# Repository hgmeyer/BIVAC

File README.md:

# BIVAC
While navigating their environments it is essential for autonomous mobile systems to actively avoid collisions with obstacles. Flying insects perform this behavioural task with ease relying mainly on information the visual system provides. BIVAC (Bio-Inspired Visual Avoidance of Collisions) is a low-cost collision avoidance system based on the extraction of nearness information from visual motion. The system allows an autonomous mobile agent to navigate in cluttered environments while actively avoiding obstacles.

**Please note:** This is the repository for a project that will be hosted on [hackaday.io](http://hackaday.io/). Please visit the [project page](https://hackaday.io/project/13301-bivac-bio-inspired-visual-collision-avoidance/) for more information.

<br />This work is licensed under a <a rel="license" href="http://creativecommons.org/licenses/by-sa/4.0/">Creative Commons Attribution-ShareAlike 4.0 International License</a>.

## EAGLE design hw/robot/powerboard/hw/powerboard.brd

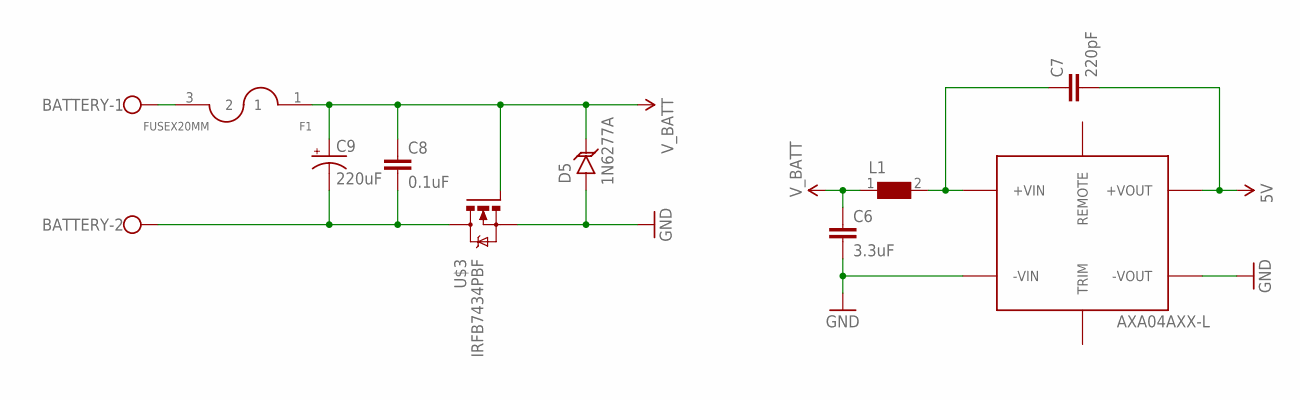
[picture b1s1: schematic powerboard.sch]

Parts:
BATTERY: W237-102
C6: 3.3uF; 1210
C7: 220pF; C1808
C8: 0.1uF; 0603-CAP
C9: 220uF; PANASONIC_G
D5: 1N6277A
F1: FUSEX20MM; FUSE_5MM
L1: WE-HCI-744314650_7030/7040/7050; WE-HCI_7030/7040/7050
U$2: AXA04AXX-L
U$3: IRFB7434PBF

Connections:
5V: C7.2, U$2.+VOUT
GND: C6.2, D5.A, U$2.-VIN, U$2.-VOUT, U$3.SOURCE (S)
unnamed: C7.1, L1.2, U$2.+VIN
unnamed: BATTERY.1, F1.3 (2)
unnamed: BATTERY.2, C8.2, C9.-, U$3.DRAIN (D)
V_BATT: C6.1, C8.1, C9.+, D5.C, F1.1, L1.1, U$3.GATE (G)

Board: 2 copper layers, 10 parts (0 on the bottom side), 6 nets, no tracks yet.

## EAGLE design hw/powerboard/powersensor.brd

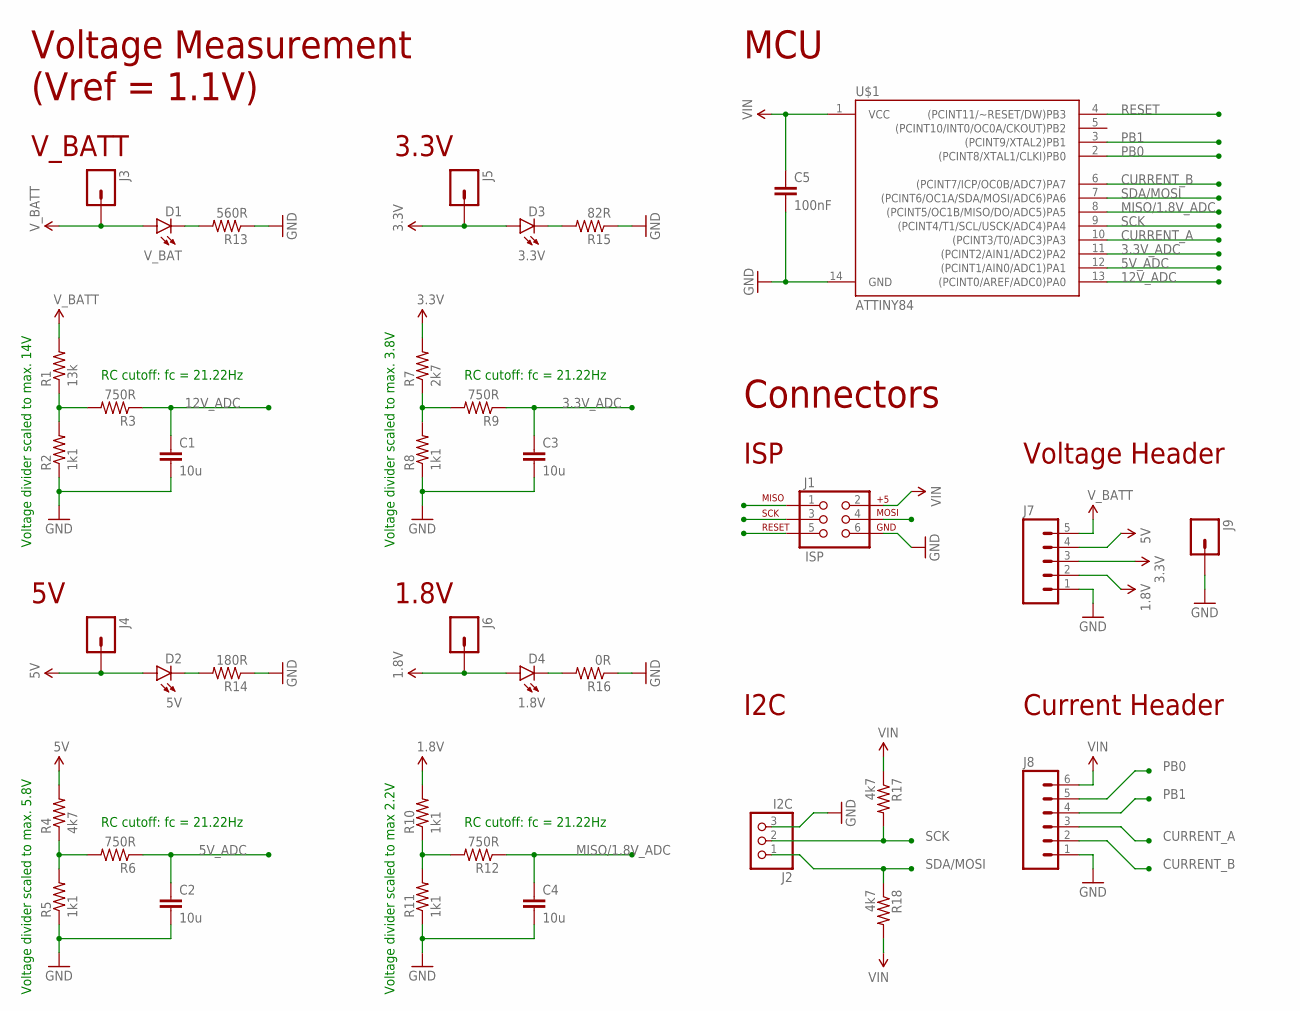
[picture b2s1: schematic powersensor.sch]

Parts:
C1, C2, C3, C4: 10u; 0603-CAP
C5: 100nF; 0603-CAP
D1: V_BAT; LED-0603
D2: 5V; LED-0603
D3: 3.3V; LED-0603
D4: 1.8V; LED-0603
J1: ISP; 2X3
J2: I2C; 1X03/90
J3, J4, J5, J6, J9: M01PTH; 1X01
J7: M05PTH; 1X05
J8: M06SILK_FEMALE_PTH; 1X06
R1: 13k; 0603-RES
R2, R5, R8, R10, R11: 1k1; 0603-RES
R3, R6, R9, R12: 750R; 0603-RES
R4, R17, R18: 4k7; 0603-RES
R7: 2k7; 0603-RES
R13: 560R; 0603-RES
R14: 180R; 0603-RES
R15: 82R; 0603-RES
R16: 0R; 0603-RES
U$1: ATTINY84; SO14

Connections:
1.8V: D4.A, J6.1, J7.2, R10.2
3.3V: D3.A, J5.1, J7.3, R7.2
3.3V_ADC: C3.1, R9.1, U$1.11 ((PCINT2/AIN1/ADC2)PA2)
5V: D2.A, J4.1, J7.4, R4.2
5V_ADC: C2.1, R6.1, U$1.12 ((PCINT1/AIN0/ADC1)PA1)
12V_ADC: C1.1, R3.1, U$1.13 ((PCINT0/AREF/ADC0)PA0)
CURRENT_A: J8.3, U$1.10 ((PCINT3/T0/ADC3)PA3)
CURRENT_B: J8.2, U$1.6 ((PCINT7/ICP/OC0B/ADC7)PA7)
GND: C1.2, C2.2, C3.2, C4.2, C5.2, J1.6, J2.3, J7.1, J8.1, J9.1, R2.1, R5.1, R8.1, R11.1, R13.1, R14.1, R15.1, R16.1, U$1.14 (GND)
MISO/1.8V_ADC: C4.1, J1.1, R12.1, U$1.8 ((PCINT5/OC1B/MISO/DO/ADC5)PA5)
unnamed: R1.1, R2.2, R3.2
unnamed: R4.1, R5.2, R6.2
unnamed: R7.1, R8.2, R9.2
unnamed: R10.1, R11.2, R12.2
unnamed: D1.C, R13.2
unnamed: D2.C, R14.2
unnamed: D3.C, R15.2
unnamed: D4.C, R16.2
PB0: J8.5, U$1.2 ((PCINT8/XTAL1/CLKI)PB0)
PB1: J8.4, U$1.3 ((PCINT9/XTAL2)PB1)
RESET: J1.5, U$1.4 ((PCINT11/~RESET/DW)PB3)
SCK: J1.3, J2.2, R17.2, U$1.9 ((PCINT4/T1/SCL/USCK/ADC4)PA4)
SDA/MOSI: J1.4, J2.1, R18.1, U$1.7 ((PCINT6/OC1A/SDA/MOSI/ADC6)PA6)
VIN: C5.1, J1.2, J8.6, R17.1, R18.2, U$1.1 (VCC)
V_BATT: D1.A, J3.1, J7.5, R1.2

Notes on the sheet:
Voltage divider scaled to max. 14V
Voltage divider scaled to max. 3.8V
Voltage divider scaled to max 2.2V
Voltage divider scaled to max. 5.8V
V_BATT
3.3V
1.8V
Voltage Measurement (Vref = 1.1V)
MCU
ISP
Connectors
I2C
Voltage Header
Current Header
RC cutoff: fc = 21.22Hz

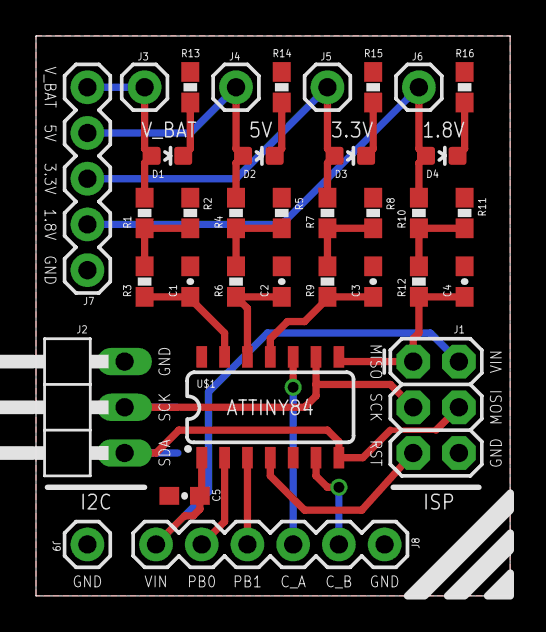
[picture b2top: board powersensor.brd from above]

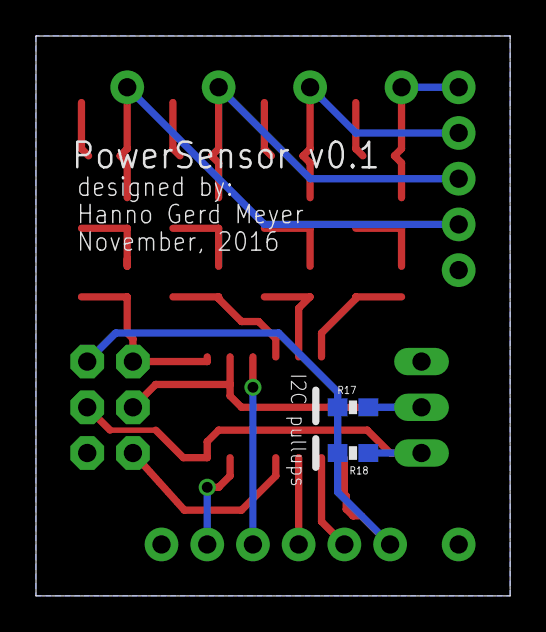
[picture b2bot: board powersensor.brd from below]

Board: 2 copper layers, 26.3 x 31.1 mm, 37 parts (2 on the bottom side), 25 nets.

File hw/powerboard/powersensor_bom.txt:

Qty Value    Device             Package  Parts                Description                   PROD_ID   
5            M01PTH             1X01     J3, J4, J5, J6, J9   Header 1                                
1            M05PTH             1X05     J7                   Header 5                                
1            M06SILK_FEMALE_PTH 1X06     J8                   Header 6                      CONN-08437
4            RESISTOR0603-RES   0603-RES R13, R14, R15, R16   Resistor                                
1   1.8V     LED0603            LED-0603 D4                   LEDs                                    
1   100nF    CAP0603-CAP        0603-CAP C5                   Capacitor                               
4   10u      CAP0603-CAP        0603-CAP C1, C2, C3, C4       Capacitor                               
1   13k      RESISTOR0603-RES   0603-RES R1                   Resistor                                
5   1k1      RESISTOR0603-RES   0603-RES R2, R5, R8, R10, R11 Resistor                                
1   2k87     RESISTOR0603-RES   0603-RES R7                   Resistor                                
1   3.3V     LED0603            LED-0603 D3                   LEDs                                    
2   4k7      RESISTOR0603-RES   0603-RES R17, R18             Resistor                                
1   4k87     RESISTOR0603-RES   0603-RES R4                   Resistor                                
1   5V       LED0603            LED-0603 D2                   LEDs                                    
4   750R     RESISTOR0603-RES   0603-RES R3, R6, R9, R12      Resistor                                
1   ATTINY84 ATTINY84           SO14     U$1                  Atmel 14-pin 2/4/8kB flash uC IC-11285  
1   I2C      PINHD-1X3/90       1X03/90  J2                   PIN HEADER                              
1   ISP      AVR_SPI_PRG_6PTH   2X3      J1                   AVR ISP 6 Pin                           
1   V_BAT    LED0603            LED-0603 D1                   LEDs

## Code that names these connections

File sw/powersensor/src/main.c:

#include <avr/io.h>
#include <avr/interrupt.h>
#include <util/delay.h>
#include <usiTwiSlave.h>

#ifndef DEBUG
#define DEBUG 0
#endif

// Define I2C adress of slave (Note: LSB is the I2C r/w flag and must not be used for addressing!)
#define SLAVE_ADDR  0b00001000  // 0x04

// The number of ADC channels to be multiplexed
#define ADC_N       5

// ADC channel and index variables
uint8_t adc_channels[ADC_N] = {0, 1, 2, 5, 25}; // PA0, PA1, PA2, PA5, Unipolar Differential PA3 and PA7 (20x Gain)
uint8_t adc_index = 0;

// ADC buffer
uint16_t adc_buffer;
uint8_t adc_lowbyte;

void initTimer(void)
{
        // Set timer to CTC mode
        TCCR0A |= (1 << WGM01);

        // Set prescaler to 64
        TCCR0B |= (1 << CS01)|(1 << CS00);

        // Initialize counter
        TCNT0 = 0;

        // Set compare value corresponding to 500Hz (100Hz per Channel)
        OCR0A = 250;

        // Enable compare interrupt
        TIMSK0 |= (1 << OCIE0A);
}

void initADC(void)
{
        // Set reference voltage to 1.1V
        ADMUX |= (1 << REFS1);

        // Clear MUX0:5 and set adc channel according to current index
        ADMUX = (ADMUX & ~(0x3F)) | (adc_channels[adc_index] & 0x3F);

        // Enable ADC
        ADCSRA |= (1 << ADEN);

        // Set prescaler to 64 (125kHz)
        ADCSRA |= (1 << ADPS2) |
                  (1 << ADPS1);
}

ISR (TIM0_COMPA_vect)
{
        // Start ADC measurement
        ADCSRA |= (1 << ADSC);

        if(DEBUG) {
                // Toggle PB0
                PORTB ^= (1 << PB0);
        }
}

int main(void)
{

        if(DEBUG) {
                // Set PB0 and PB1 as output pins
                DDRB |= (1<<PB0) | (1<<PB1);
        }

        // Calibrate clock
        OSCCAL -= 0;

        // Disable interrupts
        cli();

        // Initialize timer
        initTimer();

        // Initialize ADC
        initADC();

        // Enable I2C slave
        usiTwiSlaveInit(SLAVE_ADDR);

        // Enable interrupts
        sei();

// Main loop
        while (1)
        {
                // If ADC measurement has been completed
                if ((ADCSRA & (1 << ADSC)) == 0)
                {
                        if (DEBUG) {
                                // Toggle PB1
                                PORTB ^= (1 << PB1);
                        }

                        // Get low byte of ADC measurement
                        adc_lowbyte = ADCL;

                        // Scale 10 Bit measurement to 16 Bit
                        adc_buffer = (ADCH << 8 | adc_lowbyte) * 64;

                        // Write ADC measurement to buffer
                        txbuffer[adc_index+adc_index] = adc_buffer;
                        txbuffer[adc_index+adc_index+1] = adc_buffer >> 8;

                        // Set ADC index
                        if (adc_index < ADC_N-1) {
                                adc_index += 1;
                        }
                        else{
                                adc_index = 0;
                        }

                        // Clear MUX0:5 and set ADC channel
                        ADMUX = (ADMUX & ~(0x3F)) | (adc_channels[adc_index] & 0x3F);

                        // Wait until next ADC measurement starts
                        while((ADCSRA & (1 << ADSC)) == 0) {}
                }
        }

        return 0;
}

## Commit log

2016-10-21 Added data for E96 resistor values
2016-10-21 Updated notebook for calculations on voltage dividers
2016-10-21 Modified voltage divider calculations to account for an internal reference voltage of 1.1V
2016-10-21 Initial commit of powerboard firmware
2016-10-21 Added section for current measurement in notebook
2016-10-21 Added TWI slave library
2016-10-21 Added preliminary main
2016-10-25 Added some application notes and datasheets for Atmel AVR MCUs
2016-10-25 Changed PlatformIO project settings to use AVR Attiny45 as build target
2016-10-25 Updated preliminary version of powerboard firmware
2016-10-26 Initial commit of EAGLE parts library for the powerboard
2016-10-26 Added datasheet of AXA04AXX-L DC/DC voltage regulator
2016-11-01 Fixed bug in TWI USI library
2016-11-01 Changed powerboard project definition to use Attiny85 for testing purposes
2016-11-01 Recent progress with powerboard firmware
2016-11-03 Initial commit of powerboard schematics and board
2016-11-03 Added text to component symbol
2016-11-03 Added inductor library
2016-11-04 Fixed pins in AXA DC/DC module package
2016-11-04 Fixed AXA DC/DC module
2016-11-05 Implemented preliminary switching between ADCs
2016-11-05 Fixed typo
2016-11-07 Recent progress with powerboard schematics
2016-11-10 Added N-channel MOSFET and TVS-diode to powerboard
2016-11-12 Initial commit of powerboard calibration script
2016-11-12 Added voltcraft submodule
2016-11-13 Initial commit of PowerSensor board. Decided to separate PowerBoard and PowerSensor.
2016-11-13 Added datasheet for AttinyX4
2016-11-13 Added programming guide for DM3000 Multimeter
2016-11-14 Added optional I2C pullups, broke out PB0/1 and performed some cosmetical changes to PowerSensor board
2016-11-14 Added values and performed some cosmetic changes on PowerSensor schematics
2016-11-14 Added preliminary powersensor BOM
2016-11-15 Fixed values and added product ids for PowerSensor BOM
2016-11-15 Added PowerSensor package to custom library
2016-11-17 Added list with breakout pins on breadboard
2016-11-17 Added simple python library submodule for SCPI communication via TMC
2016-11-17 Added .gitignore file
2016-11-22 Implemented voltage measurement and switched to ATtiny84 MCU
2016-11-22 Moved powersensor files into separate directories
2016-11-22 Implemented differential current measurement and removed unneeded volatile variables
2016-11-23 Added datasheet for MC33887 h-bridge
2016-12-07 Added analysis of powersensor input stage
2016-12-07 Initial commit of PowerSensor v0.2
2016-12-07 Added simple Arduino firmware for testing I2C output
2016-12-07 Refactored directory naming
2016-12-15 Added multiprocessing for receiving data from serial port
2016-12-15 Added missing email address
2016-12-16 Fixed missing import
2016-12-19 Changed baud- and samplerate
2016-12-19 Apply transfer function before plotting data
2016-12-19 Added script for calibrating PowerSensor board
2016-12-19 Updated notebook
2016-12-19 Updated eagle library to account for changes on power sensor board
2016-12-19 Removed cruft
2016-12-28 Renamed folder
2016-12-28 Read and show the complete sensorboard buffer
2017-01-14 Implemented read from buffer position
2017-01-14 Added calibration data
2017-01-16 Added Digilient Waveforms workbench for testing motor driver
2017-01-17 Refactored folder structure
2017-01-17 Initial commit of motorboard firmware
2017-01-19 Fixed 16-Bit PWM signal generation
2018-05-12 Added link to project page

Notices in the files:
parts and their libraries:
SparkFun-DigitalIC: Licensing: Creative Commons ShareAlike 4.0 International - https://creativecommons.org/licenses/by-sa/4.0
